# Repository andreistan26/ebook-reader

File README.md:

# OpenBook - Andrei Stan 331CC

## Descriere Functionalitate Hardware
- Tableta este controlata prin cele 3 butoane
- ESP-ul comunica cu memoria flash si SD card-ul
- Trimite date la display pentru afisarea continutului din flash/sd card
- De la USB se folosesc linia de date si cea de putere pentru alimentare
- Linia de alimentare incarca bateria tabletei
- Se folosesc protocoalele i2c si spi pentru comunicatie
- UART se poate folosi prin testpad-uri pentru debugging
## ESP32 Pini
|Pin|Semnal|Descriere|
|---|------|---------|
|EN|RESET|exact ce spune semanalul
|IO0|INT_RTC| conectat la modulul RTC care poate emite intreruperi la anumite alarme/timere
|IO1|32KHz| transmite un semanl de 32Khz care este folosit pentru ceasul tabletei
|IO2|MISO| pentru primirea datelor de la periferic (ex. SD card reader, Flash memorie)
|IO3|EPD_BUSY| pentru a trimite date numai atunci cand display-ul este gata de randat, epaper este incet, deci avem nevoie de acest semnal
|IO4|SS_SD| folosit pentru detectia sd cardului, daca este prezent
|IO5|EPD_DC| comunicatie seriala cu e-paper display-ul
|IO6|SCK| ceas pentru comunicatia SPI cu celelalte componente SPI
|IO7|MOSI| pentru transmisia informatiilor pentru card SD, memorie flash si display
|IO8|GPIO8| neutilizat
|IO9|IO/BOOT| a fost apasat butonul de pornire
|IO10|EPD_CS| Chip select pentru comunicatia seriala
|IO11|FLASH_CS| Chip select pentru memoria flash
|IO12|USB_D-| transfer de date USB diferential -
|IO13|USB_D+| transfer de date USB diferential +
|IO15|IO/Change| butonul de schimbat pagina este apasat
|TXD0| TX| Tx pe UART, este folosit numai la testpad-uri pentru debugging
|RXD0| RX| Rx pe UART, este folosit numai la testpad-uri  pentru debugging
|IO18| RTC_RST| resetare a ceasului de 32Khz
|IO19| I2C_PW| alimentare si chip-select pentru senzor
|IO20| EPD_3v3_c| controleaza transzistorul prin care este alimentat display-ul (nu putem alimenta direct din el sau cel putin e bad practice)
|IO21| SDA| linie de date pentru comunicarea i2c 
|IO22| SCL| semnalul de ceas pentru comunicatrea i2c
|IO23| EPD_RST| resetare a display-ului

## Design Log \ Decizii

* Mufa USB a fost modificata pentru a evita erorile DRC
* Traseele de putere au fost facute prima data, dupa care am folosit autorouter-ul pentru a completa
* Am mutat toate gaurile de pe carcasa si dimensiunile acesteia pentru a intra PCB ul

## BOM
|Qty|Device|Parts|DATASHEET|DESCRIPTION|MOUSER_PRICE-STOCK|
|---|------|-----|---------|-----------|------------------|
|1|ADAFRUIT_LEDCHIP-LED0603|CHG_LED|https://www.vishay.com/doc?82437||https://ro.mouser.com/ProductDetail/Vishay-Semiconductors/VLMY1301-GS08?qs=sGAEpiMZZMusoohG2hS%252B168PbK3WnfgfiGSE4pxVBaDPiKIho6Ieew%3D%3D|
|1|ESP32_WROVER_EAGLE-LTSPICE_RR0402|R15|https://www.vishay.com/doc?20035||https://ro.mouser.com/ProductDetail/Vishay-Dale/CRCW040240K2FKED?qs=rzhQWu8UUS3g49JmcwYN7w%3D%3D&utm_id=20109199409&utm_source=google&utm_medium=cpc&utm_marketing_tactic=emeacorp&gad_source=1&gclid=EAIaIQobChMI4vv9kZaojAMV7YKDBx2W9Ae5EAAYAiAAEgK9cfD_BwE|
|1|ESP32_WROVER_EAGLE-LTSPICE_RR0402|R21|https://www.vishay.com/doc?20035|||
|7|EAGLE-LTSPICE_CC0402|"C3, C4, C5, C9, C18, C19, C_DELAY"|https://ro.mouser.com/datasheet/2/447/KEM_C1006_X5R_SMD-3316465.pdf||https://ro.mouser.com/ProductDetail/KEMET/C0402C475K8PACTU?qs=sGAEpiMZZMsh%252B1woXyUXj%252BeMYF%2FJh1ZHWLnD7xub%252BoY%3D|
|2|ESP32_WROVER_EAGLE-LTSPICE_CC0402|"C24, C25"|https://ro.mouser.com/datasheet/2/447/KEM_C1006_X5R_SMD-3316465.pdf||https://ro.mouser.com/ProductDetail/KEMET/C0402C475K8PACTU?qs=sGAEpiMZZMsh%252B1woXyUXj%252BeMYF%2FJh1ZHWLnD7xub%252BoY%3D|
|1|RCL_CPOL-EUCT3528|C28|https://ro.mouser.com/datasheet/2/447/KEM_T2073_T59X-3316825.pdf||https://ro.mouser.com/ProductDetail/KEMET/T598B335M035ATE150?qs=sGAEpiMZZMsh%252B1woXyUXj9kQnrMN1UR3%252B%2FX%2FiUkAw%2Fg%3D|
|1|ESP32_WROVER_EAGLE-LTSPICE_RR0402|R14|https://www.vishay.com/doc?20035||https://ro.mouser.com/ProductDetail/Vishay-Dale/CRCW040240K2FKED?qs=rzhQWu8UUS3g49JmcwYN7w%3D%3D&utm_id=20109199409&utm_source=google&utm_medium=cpc&utm_marketing_tactic=emeacorp&gad_source=1&gclid=EAIaIQobChMI4vv9kZaojAMV7YKDBx2W9Ae5EAAYAiAAEgK9cfD_BwE|
|12|ESP32_WROVER_EAGLE-LTSPICE_RR0402|"R1, R1_PINH1, R2, R2_PINH1, R3, R5, R6, R7, R8, R10, R11, R17"|https://www.vishay.com/doc?20035|||
|3|ESP32_WROVER_EAGLE-LTSPICE_RR0402|"R_BOOT, R_CHANGE, R_RESET"|https://www.vishay.com/doc?20035|||
|1|ESP32_WROVER_EAGLE-LTSPICE_CC0402|C21|https://ro.mouser.com/datasheet/2/447/KEM_C1006_X5R_SMD-3316465.pdf||https://ro.mouser.com/ProductDetail/KEMET/C0402C475K8PACTU?qs=sGAEpiMZZMsh%252B1woXyUXj%252BeMYF%2FJh1ZHWLnD7xub%252BoY%3D|
|1|112A-TAAR-R03_ATTEND|J1|https://www.attend.com.tw/data/download/file/112A-TAAR-R03_Spec.pdf|"Micro SD Card Socket, Push-Push Type, Top Mount, SMT, H=1.83mm, 10u"|https://www.digikey.com/en/products/detail/attend-technology/112A-TAAR-R03/17633923|
|1|ESP32_WROVER_EAGLE-LTSPICE_RR0402|R_CAPACITOR|https://www.vishay.com/doc?20035|||
|1|EAGLE-LTSPICE_CC0402|C2|https://ro.mouser.com/datasheet/2/447/KEM_C1006_X5R_SMD-3316465.pdf||https://ro.mouser.com/ProductDetail/KEMET/C0402C475K8PACTU?qs=sGAEpiMZZMsh%252B1woXyUXj%252BeMYF%2FJh1ZHWLnD7xub%252BoY%3D|
|10|EAGLE-LTSPICE_CC0402|"C7, C8, C10, C11, C12, C13, C14, C15, C16, C17"|https://ro.mouser.com/datasheet/2/447/KEM_C1006_X5R_SMD-3316465.pdf||https://ro.mouser.com/ProductDetail/KEMET/C0402C475K8PACTU?qs=sGAEpiMZZMsh%252B1woXyUXj%252BeMYF%2FJh1ZHWLnD7xub%252BoY%3D|
|1|ESP32_WROVER_EAGLE-LTSPICE_RR0402|R12|https://www.vishay.com/doc?20035|||
|1|ESP32_WROVER_EAGLE-LTSPICE_RR0402|R1_BAT|https://www.vishay.com/doc?20035|||
|1|ESP32_WROVER_SPARKFUN-DISCRETESEMI_MOSFET_PCH-DMG2305UX-7|Q1|https://www.diodes.com/assets/Datasheets/DMG2305UX.pdf||https://www.digikey.ro/en/products/detail/diodes-incorporated/DMG2305UX-7/4340667|
|1|ESP32_WROVER_SPARKFUN-DISCRETESEMI_MOSFET_PCH-DMG2305UX-7|Q3|https://www.diodes.com/assets/Datasheets/DMG2305UX.pdf||https://www.digikey.ro/en/products/detail/diodes-incorporated/DMG2305UX-7/4340667|
|1|ESP32_WROVER_EAGLE-LTSPICE_RR0402|R16|https://www.vishay.com/doc?20035|||
|2|EAGLE-LTSPICE_CC0402|"C22, C23"|https://ro.mouser.com/datasheet/2/447/KEM_C1006_X5R_SMD-3316465.pdf||https://ro.mouser.com/ProductDetail/KEMET/C0402C475K8PACTU?qs=sGAEpiMZZMsh%252B1woXyUXj%252BeMYF%2FJh1ZHWLnD7xub%252BoY%3D|
|2|ESP32_WROVER_EAGLE-LTSPICE_CC0402|"C26, C27"|https://ro.mouser.com/datasheet/2/447/KEM_C1006_X5R_SMD-3316465.pdf||https://ro.mouser.com/ProductDetail/KEMET/C0402C475K8PACTU?qs=sGAEpiMZZMsh%252B1woXyUXj%252BeMYF%2FJh1ZHWLnD7xub%252BoY%3D|
|1|ESP32_WROVER_EAGLE-LTSPICE_CC0402|C20|https://ro.mouser.com/datasheet/2/447/KEM_C1006_X5R_SMD-3316465.pdf||https://ro.mouser.com/ProductDetail/KEMET/C0402C475K8PACTU?qs=sGAEpiMZZMsh%252B1woXyUXj%252BeMYF%2FJh1ZHWLnD7xub%252BoY%3D|
|2|ESP32_WROVER_EAGLE-LTSPICE_RR0402|"R19, R20"|https://www.vishay.com/doc?20035|||
|1|744043680IND_4828-WE-TPC_WRE|L3|https://www.we-online.com/components/products/datasheet/744043680.pdf||https://ro.mouser.com/ProductDetail/Wurth-Elektronik/744043680?qs=PGXP4M47uW6VkZq%252BkzjrHA%3D%3D&srsltid=AfmBOoq3PLABygfB0-85eEKpA9SffUYwty425nbkhbFJ01kDNoAxFF7J|
|1|BD5229G-TR|IC1|https://fscdn.rohm.com/en/products/databook/datasheet/ic/power/voltage_detector/bd52xxg-e.pdf|"Voltage Detector with Adjustable Delay Time: CMOS processes are utilized to develop high precision  low current consumption CMOS reset ICs that allow arbitrary setting of the delay time. The extensive lineup includes both Nch Open Drain and CMOS output types in a wide range of detection voltages (from 2.3V to 6.0V, in 0.1V steps) enabling selection of the ideal solution based on customer requirements. In addition the entire series is of course both lead-free and RoHS-compliant."|https://www.mouser.co.uk/ProductDetail/ROHM-Semiconductor/BD5229G-TR?qs=4kLU8WoGk0vvnhrrYwdszw%3D%3D|
|1|ESP32_WROVER_BME680_BME680|SENSOR2|https://ro.mouser.com/datasheet/2/783/BST_BME680_DS001-1509608.pdf| Integrated Environmental Unit |https://ro.mouser.com/ProductDetail/Bosch-Sensortec/BME680?qs=v271MhAjFHjo0yA%2FC4OnDQ%3D%3D|
|3|BUTTON_CUSYOMV1|"BOOT_BUTTON, CHANGE_BUTTON, RESET_BUTTON"|https://4donline.ihs.com/images/VipMasterIC/IC/PANA/PANAS45028/PANAS45028-1.pdf?hkey=CECEF36DEECDED6468708AAF2E19C0C6||https://ro.mouser.com/ProductDetail/Panasonic/EVQ-9P701P?qs=NPkb10g2yLBKCwpELvsGNg%3D%3D|
|1|CPH3225A|C6|https://mm.digikey.com/Volume0/opasdata/d220001/medias/docus/6537/rev05-CPHCPM.pdf| 11 mF (EDLC) Supercapacitor 3.3 V 1210 (3225 Metric) - - ||
|1|DS3231SN#|U4|https://ro.mouser.com/datasheet/2/609/DS3231-3421123.pdf| Extremely Accurate I C-Integrated RTC/TCXO/Crystal ||
|1|ESP32-C6-WROOM-1-N8|U1|https://www.espressif.com/sites/default/files/documentation/esp32-c6-wroom-1_wroom-1u_datasheet_en.pdf|" Multiprotocol Modules ESP32-C6 module, Wi-Fi 6 in 2.4 GHz band, Bluetooth 5, Zigbee 3.0 and Thread. ESP34-WROOM Compatible - ENGINEERING SAMPLE "||
|1|ESP32C6_VARISTORCN1812|R18|https://mm.digikey.com/Volume0/opasdata/d220001/medias/docus/2123/CTVS_Standard_Rev2015.pdf||https://www.digikey.be/en/products/detail/epcos-tdk-electronics/CN1812K11G/635074?srsltid=AfmBOora8jXqSIsuJ5wbLbjXOKEBe4X6EtjlDXrR_O7ItUtFQ009LUoi|
|2|ESP32_WROVER_AVX---SD0805S020S1R0_AVX_SD0805S020S1R0_0_0AVX_SD0805S020S1R0_0_0|"D1, D13"|http://datasheets.avx.com/schottky.pdf|||
|1|ESP32_WROVER_SPARKFUN-IC-POWER_MCP73831|MCP73831|https://ro.mouser.com/datasheet/2/268/MCP73831_Family_Data_Sheet_DS20001984H-3441711.pdf||https://www.mouser.dk/ProductDetail/Microchip-Technology/MCP73831T-3ACI-OT?qs=yUQqVecv4quInAWkk8YFWg%3D%3D|
|1|FH34SRJ-24S-0.5SH_99_|J3|https://ro.mouser.com/datasheet/2/185/FH34SRJ_24S_0_5SH_99__CL0580_1255_6_99_2DDrawing_0-1615044.pdf|"24 Position FFC, FPC Connector Contacts, Top and Bottom 0.020"" (0.50mm) Surface Mount, Right Angle"|https://www.mouser.co.uk/ProductDetail/Hirose-Connector/FH34SRJ-24S-0.5SH99?qs=vcbW%252B4%252BSTIpKBl5ap9J8Fw%3D%3D|
|1|MAX17048G+T10|U2|https://ro.mouser.com/datasheet/2/609/MAX17048_MAX17049-3469099.pdf| 3 A 1-Cell/2-Cell Fuel Gauge with ModelGauge ||
|3|MBR0530|"D3, D5, D7"|https://www.onsemi.cn/pdf/datasheet/mbr0530-d.pdf| Diode Schottky 30 V 500mA Surface Mount SOD-123 ||
|6|PGB1010603MR|"D2, D4, D6, D8, D10, D11"|https://www.littelfuse.com/assetdocs/pulseguard-esd-suppressors-pgb1-datasheet?assetguid=8a337998-d54d-466b-be4e-dc5bcd1f9321| 150V (Typ) Clamp - Ipp Tvs Diode Surface Mount 0603 (1608 Metric) ||
|1|QWIIC_CONNECTORJS-1MM|J2|https://ro.mouser.com/datasheet/2/813/Qwiic_Connector_Datasheet-1223982.pdf||https://ro.mouser.com/ProductDetail/SparkFun/PRT-14417?qs=wd5RIQLrsJhgdz%2FpmZ%2F3GQ%3D%3D&srsltid=AfmBOoqQ1oOwS9wen4cUg5-iBLh8Bm57R1iVLhkDmOc94Djde0aRxIcK|
|1|SAMACSYS_PARTS_USB4110-GF-A|J4|https://ro.mouser.com/datasheet/2/837/GCT_USB4110_Product_Drawing___20k_cycles-3455479.pdf|CONN USB 2.0 TYPE-C R/A SMT|https://www.mouser.co.uk/ProductDetail/GCT/USB4110-GF-A?qs=KUoIvG%2F9IlYiZvIXQjyJeA%3D%3D|
|1|SI1308EDL-T1-GE3|Q2|https://www.vishay.com/docs/63399/si1308edl.pdf|" Si1308EDL-T1-GE3 N-channel MOSFET Transistor, 1.5 A, 30 V, 3-Pin SC-70 Siliconix / Vishay SI1308EDL-T1-GE3 "||
|1|USBLC6-2SC6Y|D9|https://ro.mouser.com/datasheet/2/389/usblc6_2sc6y-1852505.pdf| 17V Clamp 5A (8/20 s) Ipp Tvs Diode Surface Mount SOT-23-6 |https://ro.mouser.com/ProductDetail/STMicroelectronics/USBLC6-2SC6Y?utm_campaign=mouser&qs=gNDSiZmRJS%2FOgDexvXkdow==&utm_medium=online&utm_source=snapedaonline&utm_content=model|
|1|W25Q512JVEIQ|U3|https://www.winbond.com/resource-files/W25Q512JV%20SPI%20RevB%2006252019%20KMS.pdf| FLASH - NOR Memory IC 512Mb (64M x 8) SPI - Quad I/O 133 MHz 8-WSON (8x6) ||
|1|XC6220A331MR-G|IC2|https://ro.mouser.com/datasheet/2/760/xc6220-3371556.pdf|LDO Voltage Regulators|https://www.mouser.co.uk/ProductDetail/Torex-Semiconductor/XC6220A331MR-G?qs=AsjdqWjXhJ8ZSWznL1J0gg%3D%3D|

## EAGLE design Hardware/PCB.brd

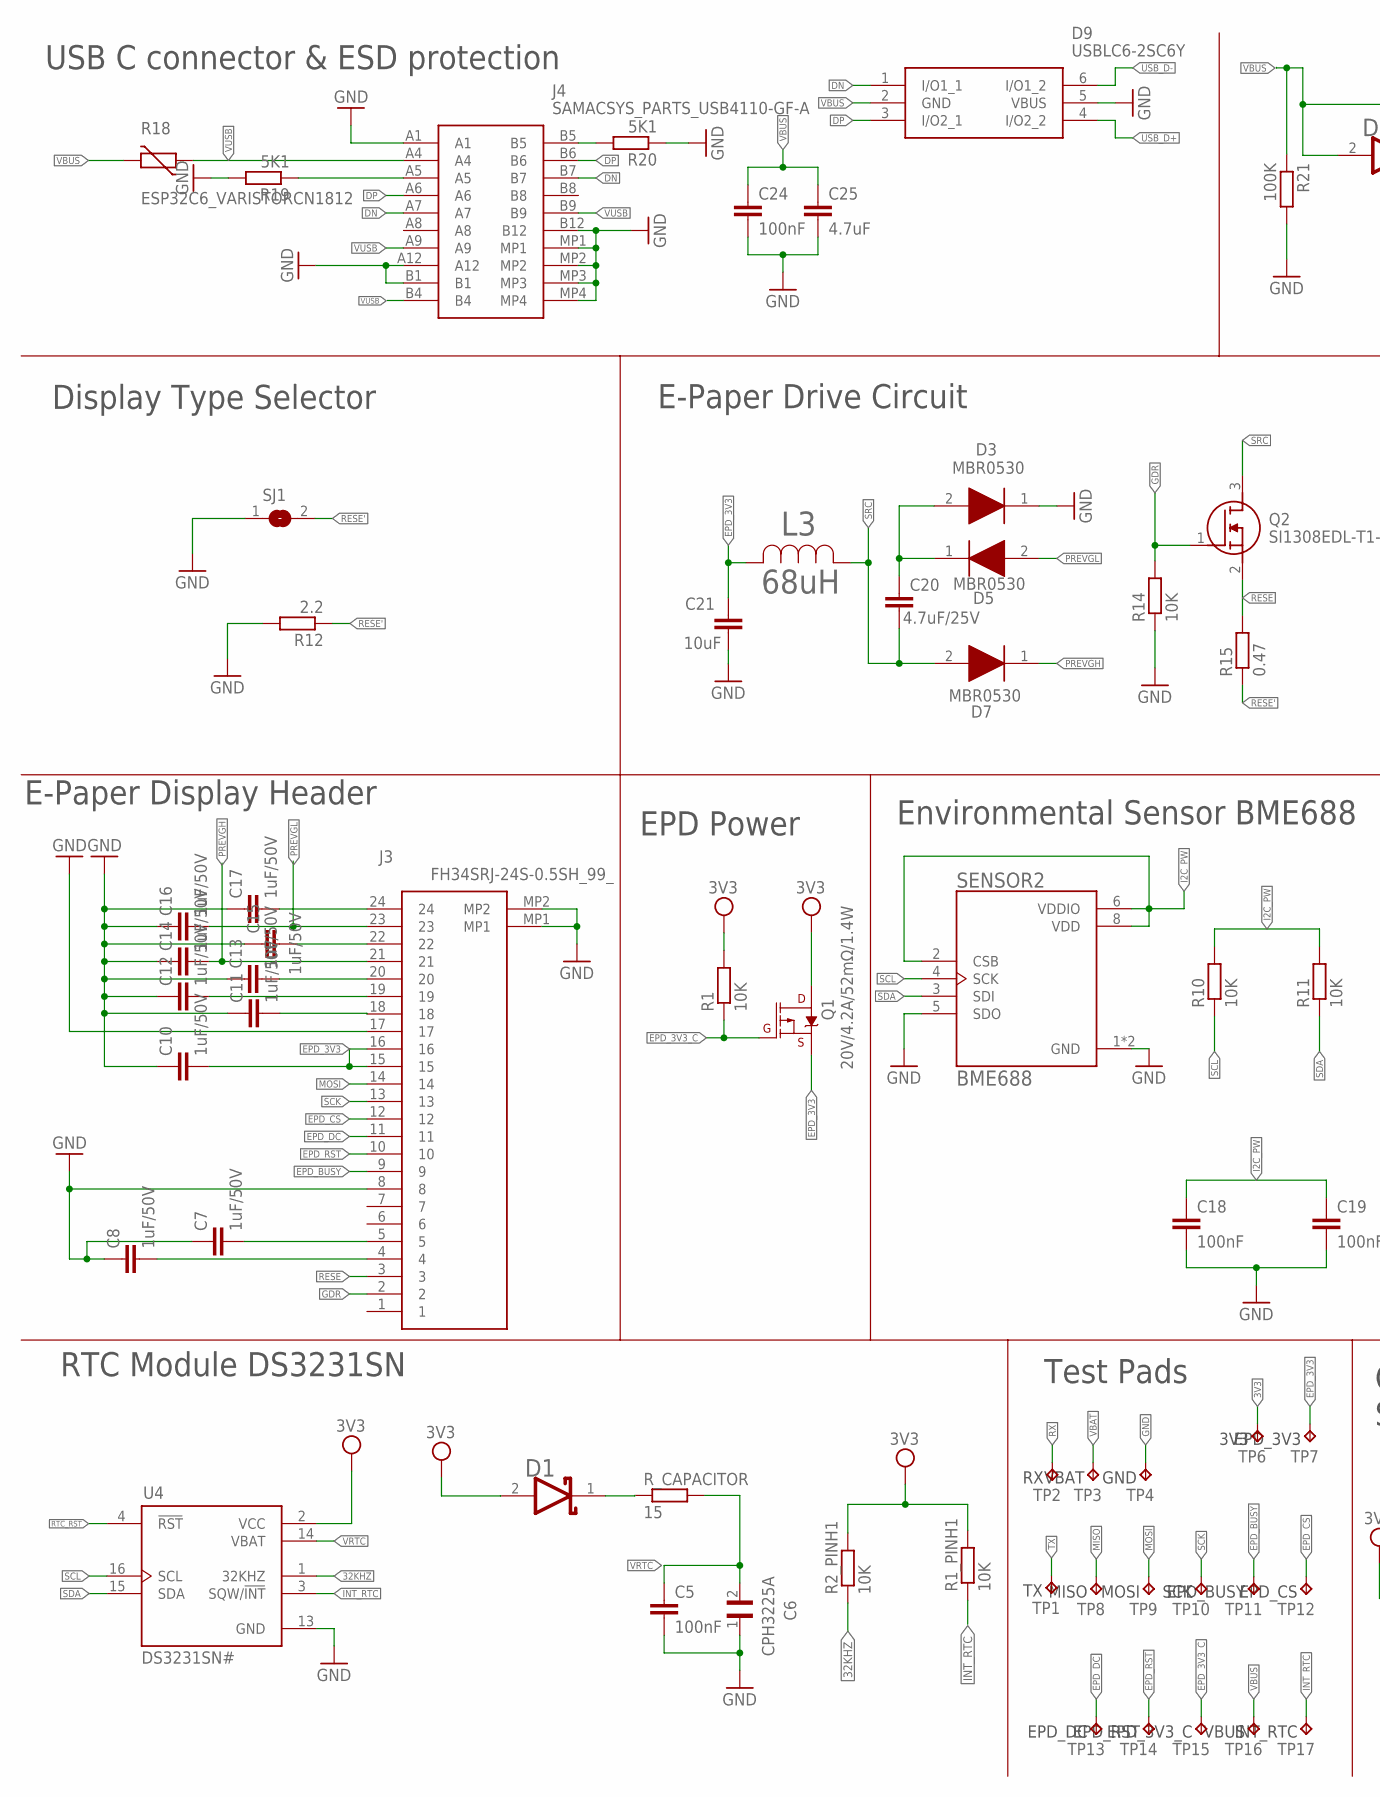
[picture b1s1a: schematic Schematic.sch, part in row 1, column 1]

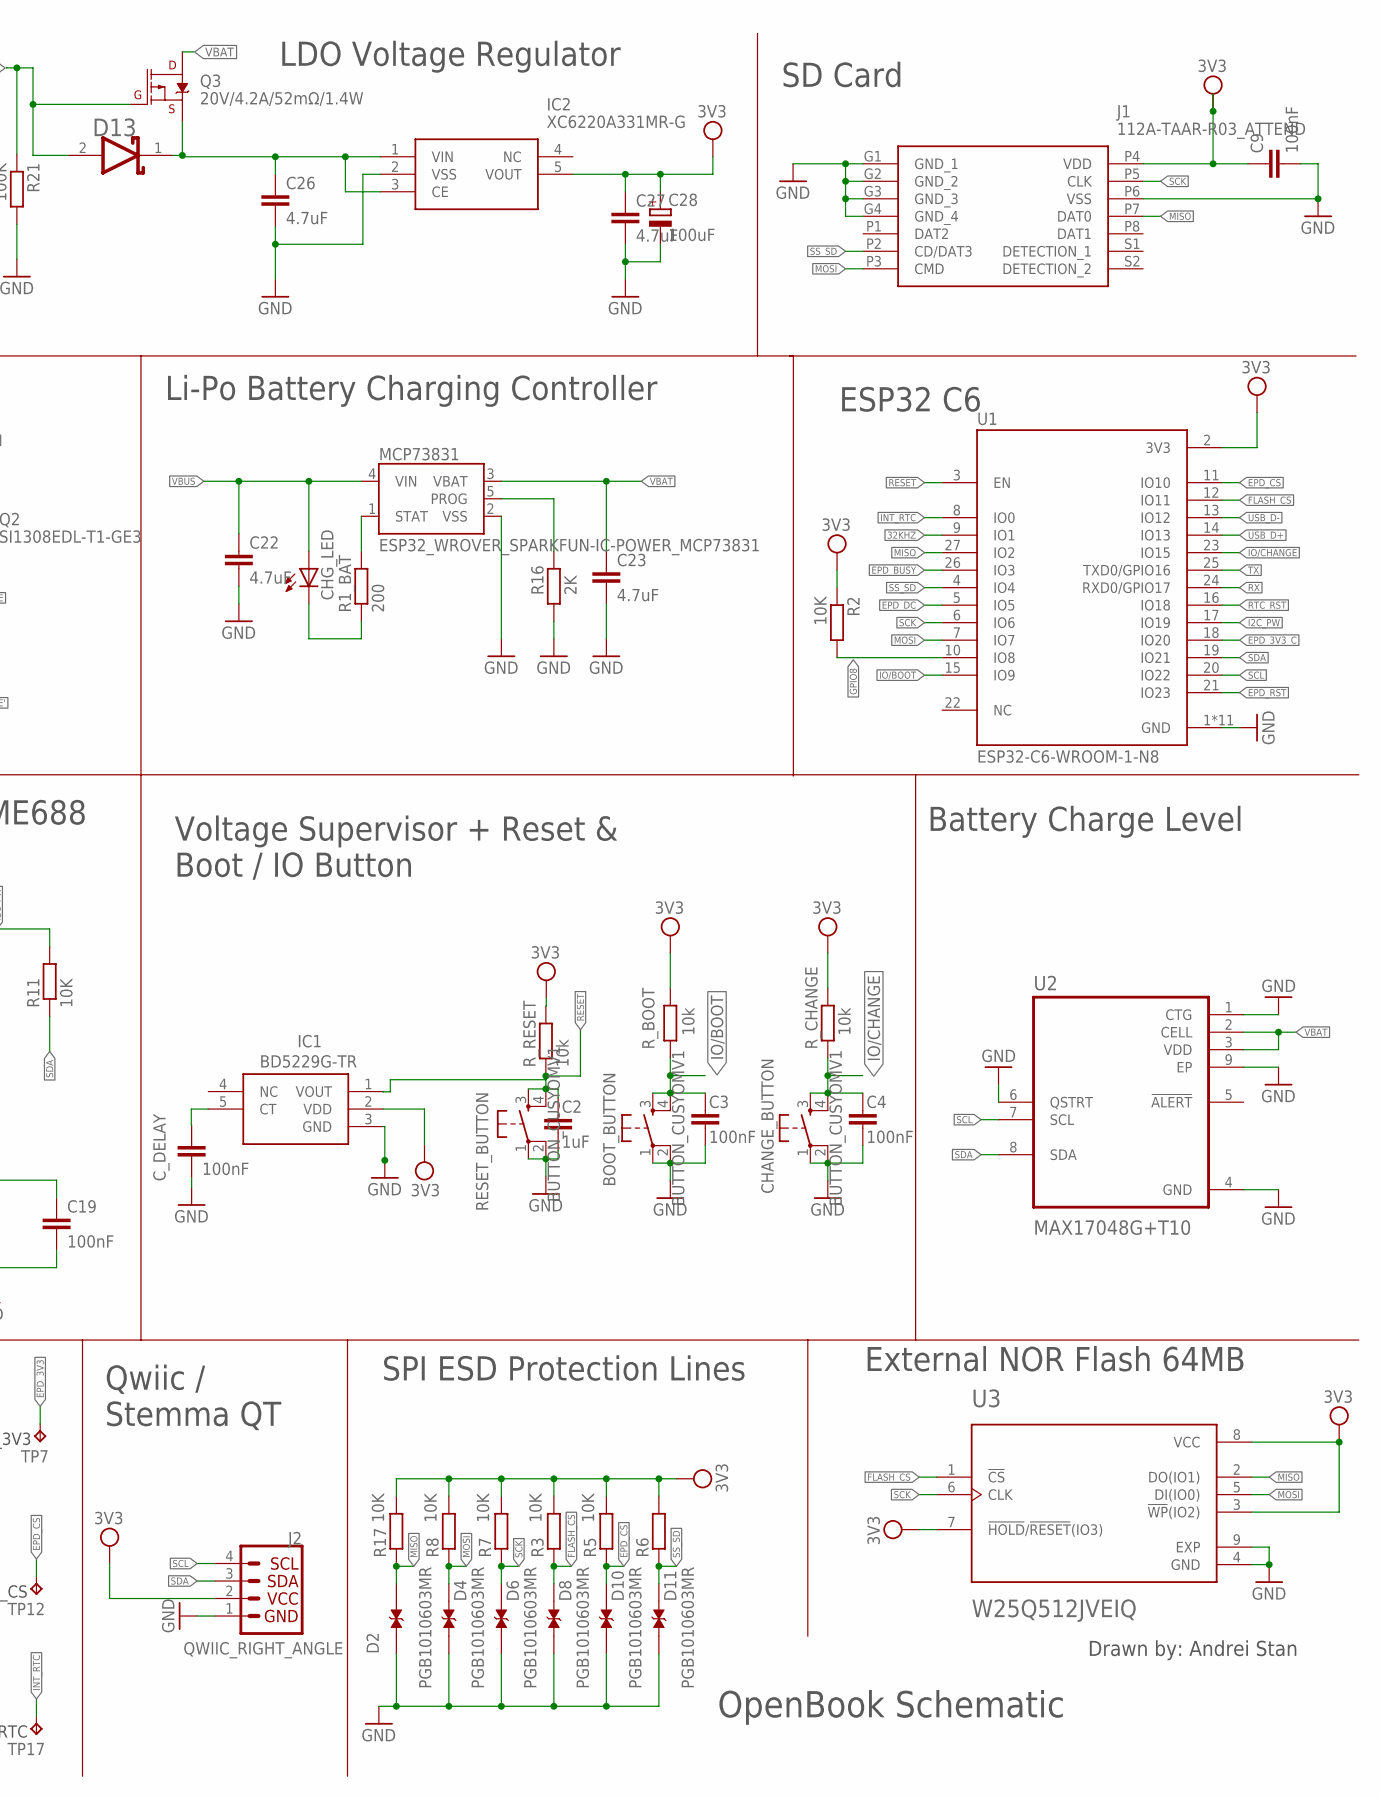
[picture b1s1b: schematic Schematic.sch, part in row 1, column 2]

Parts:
BOOT_BUTTON: BUTTON_CUSYOMV1; MYBUTTON
C2: 1uF; EAGLE-LTSPICE_C0402
C3, C4, C5, C9, C18, C19: 100nF; EAGLE-LTSPICE_C0402
C6: CPH3225A; CAPCP3225X100N
C7, C8, C10, C11, C12, C13, C14, C15, C16, C17: 1uF/50V; EAGLE-LTSPICE_C0402
C20: 4.7uF/25V; ESP32_WROVER_EAGLE-LTSPICE_C0402
C21: 10uF; ESP32_WROVER_EAGLE-LTSPICE_C0402
C22, C23: 4.7uF; EAGLE-LTSPICE_C0402
C24: 100nF; ESP32_WROVER_EAGLE-LTSPICE_C0402
C25, C26, C27: 4.7uF; ESP32_WROVER_EAGLE-LTSPICE_C0402
C28: 100uF; RCL_CT3528
CHANGE_BUTTON: BUTTON_CUSYOMV1; MYBUTTON
CHG_LED: ADAFRUIT_LEDCHIP-LED0603; ADAFRUIT_CHIP-LED0603
C_DELAY: 100nF; EAGLE-LTSPICE_C0402
D1, D13: ESP32_WROVER_AVX---SD0805S020S1R0_AVX_SD0805S020S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; ESP32_WROVER_AVX---SD0805S020S1R0_AVX_SD0805S020S1R0_0
D2, D4, D6, D8, D10, D11: PGB1010603MR; DIOC1608X36N
D3, D5, D7: MBR0530; SOD3716X135N
D9: USBLC6-2SC6Y; SOT95P280X145-6N
IC1: BD5229G-TR; SOT95P280X125-5N
IC2: XC6220A331MR-G; SOT95P280X120-5N
J1: 112A-TAAR-R03_ATTEND; 112ATAARR03ATTEND
J2: QWIIC_RIGHT_ANGLE; JST04_1MM_RA
J3: FH34SRJ-24S-0.5SH_99_; FH34SRJ24S05SH99
J4: SAMACSYS_PARTS_USB4110-GF-A; SAMACSYS_PARTS_USB4110GFA
L3: 68uH; IND_4828-WE-TPC_WRE
MCP73831: ESP32_WROVER_SPARKFUN-IC-POWER_MCP73831; ESP32_WROVER_SPARKFUN-IC-POWER_SOT23-5
Q1, Q3: 20V/4.2A/52mΩ/1.4W; ESP32_WROVER_SPARKFUN-DISCRETESEMI_SOT23-3
Q2: SI1308EDL-T1-GE3; SOT65P210X110-3N
R1, R1_PINH1, R2, R2_PINH1, R3, R5, R6, R7, R8, R10, R11, R14, R17: 10K; ESP32_WROVER_EAGLE-LTSPICE_R0402
R1_BAT: 200; ESP32_WROVER_EAGLE-LTSPICE_R0402
R12: 2.2; ESP32_WROVER_EAGLE-LTSPICE_R0402
R15: 0.47; ESP32_WROVER_EAGLE-LTSPICE_R0402
R16: 2K; ESP32_WROVER_EAGLE-LTSPICE_R0402
R18: ESP32C6_VARISTORCN1812; ESP32C6_VARISTOR_CT/CN1812
R19, R20: 5K1; ESP32_WROVER_EAGLE-LTSPICE_R0402
R21: 100K; ESP32_WROVER_EAGLE-LTSPICE_R0402
RESET_BUTTON: BUTTON_CUSYOMV1; MYBUTTON
R_BOOT: 10k; ESP32_WROVER_EAGLE-LTSPICE_R0402
R_CAPACITOR: 15; ESP32_WROVER_EAGLE-LTSPICE_R0402
R_CHANGE: 10k; ESP32_WROVER_EAGLE-LTSPICE_R0402
R_RESET: 10k; ESP32_WROVER_EAGLE-LTSPICE_R0402
SENSOR2: BME688; ESP32_WROVER_BME680_PSON80P300X300X100-8N
SJ1: SJ
TP1, TP2, TP3, TP4, TP6, TP7, TP8, TP9, TP10, TP11, TP12, TP13, TP14, TP15, TP16, TP17: TPTP20R; TP20R
U1: ESP32-C6-WROOM-1-N8; XCVR_ESP32-C6-WROOM-1-N8
U2: MAX17048G+T10; SON50P200X200X80-9N
U3: W25Q512JVEIQ; SON127P600X800X80-9N
U4: DS3231SN#; SOIC127P1032X265-16N

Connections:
3V3: C9.1, C27.1, C28.+, D1.2 (ANODE), IC1.2 (VDD), IC2.5 (VOUT), J1.P4 (VDD), J2.2, Q1.3 (D), R1.2, R1_PINH1.2, R2.1, R2_PINH1.2, R3.2, R5.2, R6.2, R7.2, R8.2, R17.2, R_BOOT.2, R_CHANGE.2, R_RESET.2, TP6.TP, U1.2 (3V3), U3.3 (!WP!(IO2)), U3.7 (!HOLD!/!RESET!(IO3)), U3.8 (VCC), U4.2 (VCC)
32KHZ: R2_PINH1.1, U1.9 (IO1), U4.1 (32KHZ)
DN: D9.1 (I/O1_1), J4.A7, J4.B7
DP: D9.3 (I/O2_1), J4.A6, J4.B6
EPD_3V3: C10.2, C21.1, J3.15, J3.16, L3.2, Q1.2 (S), TP7.TP
EPD_3V3_C: Q1.1 (G), R1.1, TP15.TP, U1.18 (IO20)
EPD_BUSY: J3.9, TP11.TP, U1.26 (IO3)
EPD_CS: D10.2, J3.12, R5.1, TP12.TP, U1.11 (IO10)
EPD_DC: J3.11, TP13.TP, U1.5 (IO5)
EPD_RST: J3.10, TP14.TP, U1.21 (IO23)
FLASH_CS: D8.2, R3.1, U1.12 (IO11), U3.1 (!CS)
GDR: J3.2, Q2.1 (G), R14.2
GND: BOOT_BUTTON.1, BOOT_BUTTON.2, C2.2, C3.2, C4.2, C5.2, C6.1, C7.1, C8.1, C9.2, C10.1, C11.1, C12.1, C13.1, C14.1, C15.1, C16.1, C17.1, C18.2, C19.2, C21.2, C22.2, C23.2, C24.2, C25.2, C26.2, C27.2, C28.-, CHANGE_BUTTON.1, CHANGE_BUTTON.2, C_DELAY.2, D2.1, D3.1 (K), D4.1, D6.1, D8.1, D9.5 (VBUS), D10.1, D11.1, IC1.3 (GND), IC2.2 (VSS), J1.G1 (GND_1), J1.G2 (GND_2), J1.G3 (GND_3), J1.G4 (GND_4), J1.P6 (VSS), J2.1, J3.8, J3.17, J3.MP1, J3.MP2, J4.A1, J4.A12, J4.B1, J4.B12, J4.MP1, J4.MP2, J4.MP3, J4.MP4, MCP73831.2 (VSS), R12.2, R14.1, R16.1, R19.2, R20.1, R21.2, RESET_BUTTON.1, RESET_BUTTON.2, SENSOR2.1 (GND), SENSOR2.5 (SDO), SENSOR2.7 (GND), SJ1.1, TP4.TP, U1.1 (GND), U1.28 (GND), U1.29_1 (GND), U1.29_2 (GND), U1.29_3 (GND), U1.29_4 (GND), U1.29_5 (GND), U1.29_6 (GND), U1.29_7 (GND), U1.29_8 (GND), U1.29_9 (GND), U2.1 (CTG), U2.4 (GND), U2.6 (QSTRT), U2.9 (EP), U3.4 (GND), U3.9 (EXP), U4.13 (GND)
GPIO8: R2.2, U1.10 (IO8)
I2C_PW: C18.1, C19.1, R10.2, R11.2, SENSOR2.2 (CSB), SENSOR2.6 (VDDIO), SENSOR2.8 (VDD), U1.17 (IO19)
INT_RTC: R1_PINH1.1, TP17.TP, U1.8 (IO0), U4.3 (SQW/!INT)
IO/BOOT: BOOT_BUTTON.3, BOOT_BUTTON.4, C3.1, R_BOOT.1, U1.15 (IO9)
IO/CHANGE: C4.1, CHANGE_BUTTON.3, CHANGE_BUTTON.4, R_CHANGE.1, U1.23 (IO15)
MISO: D2.2, J1.P7 (DAT0), R17.1, TP8.TP, U1.27 (IO2), U3.2 (DO(IO1))
MOSI: D4.2, J1.P3 (CMD), J3.14, R8.1, TP9.TP, U1.7 (IO7), U3.5 (DI(IO0))
unnamed: C_DELAY.1, IC1.5 (CT)
unnamed: D1.1 (CATHODE), R_CAPACITOR.1
unnamed: C8.2, J3.4
unnamed: C7.2, J3.5
unnamed: C20.1, D3.2 (A), D5.1 (K)
unnamed: MCP73831.1 (STAT), R1_BAT.2
unnamed: J4.A5, R19.1
unnamed: CHG_LED.C, R1_BAT.1
unnamed: MCP73831.5 (PROG), R16.2
unnamed: J4.B5, R20.2
unnamed: C26.1, D13.1 (CATHODE), IC2.1 (VIN), IC2.3 (CE), Q3.2 (S)
unnamed: C11.2, J3.18
unnamed: C12.2, J3.19
unnamed: C13.2, J3.20
unnamed: C15.2, J3.22
unnamed: C17.2, J3.24
PREVGH: C14.2, D7.1 (K), J3.21
PREVGL: C16.2, D5.2 (A), J3.23
RESE: J3.3, Q2.2 (S), R15.2
RESE': R12.1, R15.1, SJ1.2
RESET: C2.1, IC1.1 (VOUT), RESET_BUTTON.3, RESET_BUTTON.4, R_RESET.1, U1.3 (EN)
RTC_RST: U1.16 (IO18), U4.4 (!RST)
RX: TP2.TP, U1.24 (RXD0/GPIO17)
SCK: D6.2, J1.P5 (CLK), J3.13, R7.1, TP10.TP, U1.6 (IO6), U3.6 (CLK)
SCL: J2.4, R10.1, SENSOR2.4 (SCK), U1.20 (IO22), U2.7 (SCL), U4.16 (SCL)
SDA: J2.3, R11.1, SENSOR2.3 (SDI), U1.19 (IO21), U2.8 (SDA), U4.15 (SDA)
SRC: C20.2, D7.2 (A), L3.1, Q2.3 (D)
SS_SD: D11.2, J1.P2 (CD/DAT3), R6.1, U1.4 (IO4)
TX: TP1.TP, U1.25 (TXD0/GPIO16)
USB_D+: D9.4 (I/O2_2), U1.14 (IO13)
USB_D-: D9.6 (I/O1_2), U1.13 (IO12)
VBAT: C23.1, MCP73831.3 (VBAT), Q3.3 (D), TP3.TP, U2.2 (CELL), U2.3 (VDD)
VBUS: C22.1, C24.1, C25.1, CHG_LED.A, D9.2 (GND), D13.2 (ANODE), MCP73831.4 (VIN), Q3.1 (G), R18.2, R21.1, TP16.TP
VRTC: C5.1, C6.2, R_CAPACITOR.2, U4.14 (VBAT)
VUSB: J4.A4, J4.A9, J4.B4, J4.B9, R18.1

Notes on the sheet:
OpenBook Schematic
Drawn by: Andrei Stan
External NOR Flash 64MB
Battery Charge Level
ESP32 C6
SD Card
Qwiic / Stemma QT
SPI ESD Protection Lines
Test Pads
RTC Module DS3231SN
E-Paper Display Header
EPD Power
Voltage Supervisor + Reset & Boot / IO Button
Environmental Sensor BME688
Li-Po Battery Charging Controller
E-Paper Drive Circuit
LDO Voltage Regulator
Display Type Selector
USB C connector & ESD protection

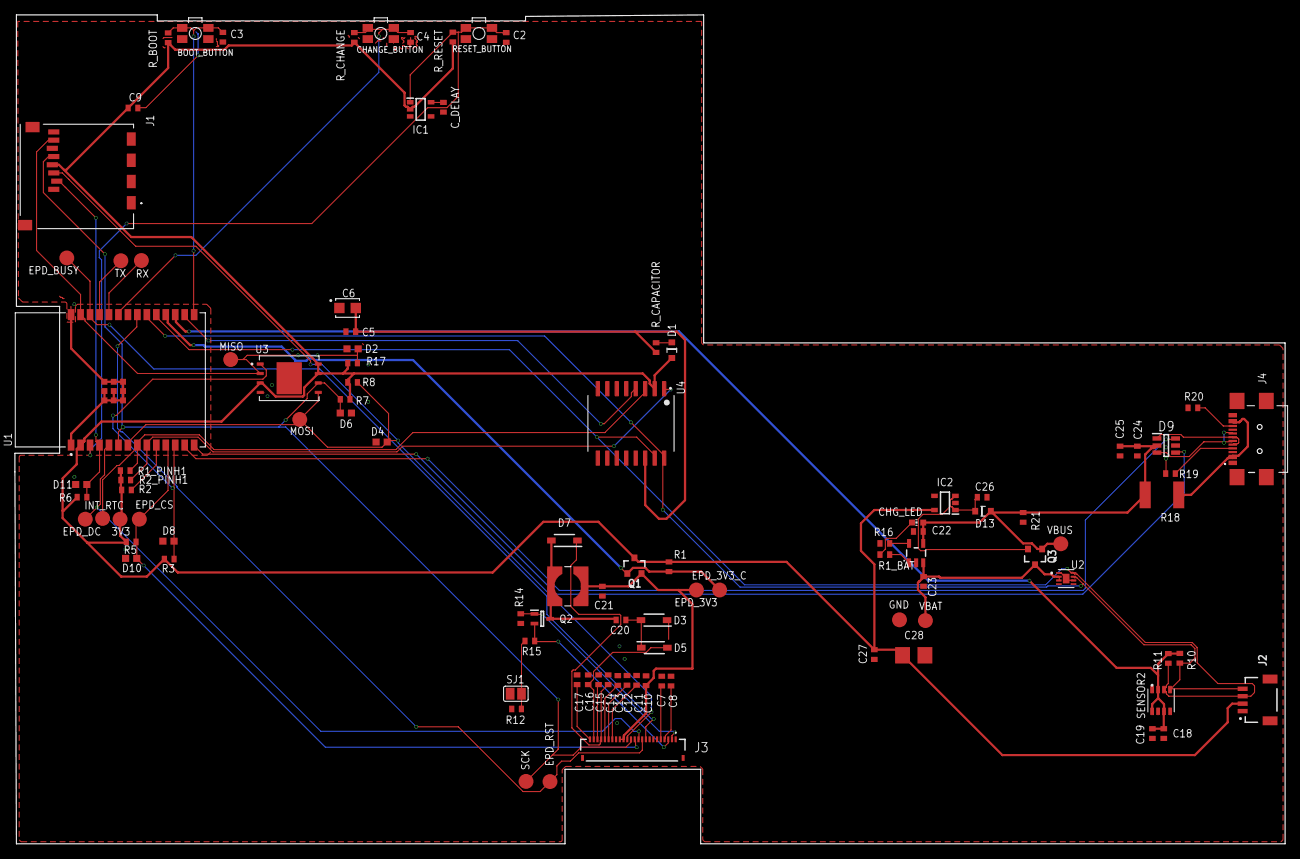
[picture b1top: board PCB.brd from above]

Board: 2 copper layers, 170.4 x 111.2 mm, 102 parts (0 on the bottom side), 55 nets.

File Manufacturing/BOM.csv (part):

Qty,Value,Device,Package,Parts,Description,ARROW_PART_NUMBER,ARROW_PRICE-STOCK,AVAILABILITY,CENTROID_NOT_SPECIFIED,CHECK_PRICES,COPYRIGHT,DATASHEET,DESCRIPTION,DIGIKEY_DESCRIPTION,DIGIKEY_PART_NUMBER,HEIGHT,LEAD_FREE,MANUFACTURER_NAME,MANUFACTURER_PART_NUMBER,MF,MFR_NAME,MOUSER_PART_NUMBER,MOUSER_PRICE-STOCK,MOUSER_TESTING_PART_NUMBER,MOUSER_TESTING_PRICE-STOCK,MP,MPN,PACKAGE,POPULARITY,PREFIX,PRICE,PROD_ID,PURCHASE-URL,ROHS,SNAPEDA_LINK,SPICEMODEL,SPICEPREFIX,TEMPERATURE_RANGE_HIGH,TEMPERATURE_RANGE_LOW,TP_SIGNAL_NAME,VALUE
1,,ADAFRUIT_LEDCHIP-LED0603,ADAFRUIT_CHIP-LED0603,CHG_LED,LED,,,,,,,https://www.vishay.com/doc?82437,,,,,,,,,,,https://ro.mouser.com/ProductDetail/Vishay-Semiconductors/VL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,,,,,,,,,,,,,,,,,,
1,,SJ,SJ,SJ1,"SMD solder JUMPER",,,,,,,,,,,,,,,,,,,,,,,,3,,,,,,,,,,,,
1,0.47,ESP32_WROVER_EAGLE-LTSPICE_RR0402,ESP32_WROVER_EAGLE-LTSPICE_R0402,R15,"RESISTOR, European symbol",,,,,,,https://www.vishay.com/doc?20035,,,,,,,,,,,https://ro.mouser.com/ProductDetail/Vishay-Dale/CRCW040240K2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,,,,,,,,,,,,,NONE,R,,,,
1,100K,ESP32_WROVER_EAGLE-LTSPICE_RR0402,ESP32_WROVER_EAGLE-LTSPICE_R0402,R21,"RESISTOR, European symbol",,,,,,,https://www.vishay.com/doc?20035,,,,,,,,,,https://eu.mouser.com/ProductDetail/Vishay-Dale/CRCW040240K2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,,,,,,,,,,,,,,NONE,R,,,,
7,100nF,EAGLE-LTSPICE_CC0402,EAGLE-LTSPICE_C0402,"C3, C4, C5, C9, C18, C19, C_DELAY","CAPACITOR, European symbol",,,,,,,https://ro.mouser.com/datasheet/2/447/KEM_C1006_X5R_SMD-3316465.pdf,,,,,,,,,,,https://ro.mouser.com/ProductDetail/KEMET/C0402C475K8PACTU?q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,,,,,,,,,,,,,NONE,C,,,,
2,100nF,ESP32_WROVER_EAGLE-LTSPICE_CC0402,ESP32_WROVER_EAGLE-LTSPICE_C0402,"C24, C25","CAPACITOR, European symbol",,,,,,,https://ro.mouser.com/datasheet/2/447/KEM_C1006_X5R_SMD-3316465.pdf,,,,,,,,,,,https://ro.mouser.com/ProductDetail/KEMET/C0402C475K8PACTU?q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,,,,,,,,,,,,,NONE,C,,,,
1,100uF,RCL_CPOL-EUCT3528,RCL_CT3528,C28,"POLARIZED CAPACITOR, European symbol",,,,,,,https://ro.mouser.com/datasheet/2/447/KEM_T2073_T59X-3316825.pdf,,,,,,,,,,,https://ro.mouser.com/ProductDetail/KEMET/T598B335M035ATE150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,,,,,,0,,,,,,,,C,,,,
1,10K,ESP32_WROVER_EAGLE-LTSPICE_RR0402,ESP32_WROVER_EAGLE-LTSPICE_R0402,R14,"RESISTOR, European symbol",,,,,,,https://www.vishay.com/doc?20035,,,,,,,,,,,https://ro.mouser.com/ProductDetail/Vishay-Dale/CRCW040240K2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,,,,,,,,,,,,,NONE,R,,,,
12,10K,ESP32_WROVER_EAGLE-LTSPICE_RR0402,ESP32_WROVER_EAGLE-LTSPICE_R0402,"R1, R1_PINH1, R2, R2_PINH1, R3, R5, R6, R7, R8, R10, R11, R17","RESISTOR, European symbol",,,,,,,https://www.vishay.com/doc?20035,,,,,,,,,,https://eu.mouser.com/ProductDetail/Vishay-Dale/CRCW040240K2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,,,,,,,,,,,,,,NONE,R,,,,
3,10k,ESP32_WROVER_EAGLE-LTSPICE_RR0402,ESP32_WROVER_EAGLE-LTSPICE_R0402,"R_BOOT, R_CHANGE, R_RESET","RESISTOR, European symbol",,,,,,,https://www.vishay.com/doc?20035,,,,,,,,,,https://eu.mouser.com/ProductDetail/Vishay-Dale/CRCW040240K2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,,,,,,,,,,,,,,NONE,R,,,,
1,10uF,ESP32_WROVER_EAGLE-LTSPICE_CC0402,ESP32_WROVER_EAGLE-LTSPICE_C0402,C21,"CAPACITOR, European symbol",,,,,,,https://ro.mouser.com/datasheet/2/447/KEM_C1006_X5R_SMD-3316465.pdf,,,,,,,,,,,https://ro.mouser.com/ProductDetail/KEMET/C0402C475K8PACTU?q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,,,,,,,,,,,,,NONE,C,,,,
1,112A-TAAR-R03_ATTEND,112A-TAAR-R03_ATTEND,112ATAARR03ATTEND,J1,"Micro SD Card Socket, Push-Push Type, Top Mount, SMT, H=1.83mm, 10u",,,,,,,https://www.attend.com.tw/data/download/file/112A-TAAR-R03_Spec.pdf,"Micro SD Card Socket"," Push-Push Type"," Top Mount"," SMT"," H=1.83mm"," 10u",,,1.9mm,,ATTEND,"112A-TAAR-R03 ATTEND",,,,https://www.digikey.com/en/products/detail/attend-technology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,,,,,,,,,,,,,
1,15,ESP32_WROVER_EAGLE-LTSPICE_RR0402,ESP32_WROVER_EAGLE-LTSPICE_R0402,R_CAPACITOR,"RESISTOR, European symbol",,,,,,,https://www.vishay.com/doc?20035,,,,,,,,,,https://eu.mouser.com/ProductDetail/Vishay-Dale/CRCW040240K2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,,,,,,,,,,,,,,NONE,R,,,,
1,1uF,EAGLE-LTSPICE_CC0402,EAGLE-LTSPICE_C0402,C2,"CAPACITOR, European symbol",,,,,,,https://ro.mouser.com/datasheet/2/447/KEM_C1006_X5R_SMD-3316465.pdf,,,,,,,,,,,https://ro.mouser.com/ProductDetail/KEMET/C0402C475K8PACTU?q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,,,,,,,,,,,,,NONE,C,,,,
10,1uF/50V,EAGLE-LTSPICE_CC0402,EAGLE-LTSPICE_C0402,"C7, C8, C10, C11, C12, C13, C14, C15, C16, C17","CAPACITOR, European symbol",,,,,,,https://ro.mouser.com/datasheet/2/447/KEM_C1006_X5R_SMD-3316465.pdf,,,,,,,,,,,https://ro.mouser.com/ProductDetail/KEMET/C0402C475K8PACTU?q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,,,,,,,,,,,,,NONE,C,,,,
1,2.2,ESP32_WROVER_EAGLE-LTSPICE_RR0402,ESP32_WROVER_EAGLE-LTSPICE_R0402,R12,"RESISTOR, European symbol",,,,,,,https://www.vishay.com/doc?20035,,,,,,,,,,https://eu.mouser.com/ProductDetail/Vishay-Dale/CRCW040240K2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,,,,,,,,,,,,,,NONE,R,,,,
1,200,ESP32_WROVER_EAGLE-LTSPICE_RR0402,ESP32_WROVER_EAGLE-LTSPICE_R0402,R1_BAT,"RESISTOR, European symbol",,,,,,,https://www.vishay.com/doc?20035,,,,,,,,,,https://eu.mouser.com/ProductDetail/Vishay-Dale/CRCW040240K2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,,,,,,,,,,,,,,NONE,R,,,,
2,20V/4.2A/52mO/1.4W,ESP32_WROVER_SPARKFUN-DISCRETESEMI_MOSFET_PCH-DMG2305UX-7,ESP32_WROVER_SPARKFUN-DISCRETESEMI_SOT23-3,"Q1, Q3","P-channel MOSFETs",,,,,,,https://www.diodes.com/assets/Datasheets/DMG2305UX.pdf,,,,,,,,,,,https://www.digikey.ro/en/products/detail/diodes-incorporate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,,,,,,,,,TRAN-14388,,,,,,,,,20V/4.2A/52mO/1.4W
1,2K,ESP32_WROVER_EAGLE-LTSPICE_RR0402,ESP32_WROVER_EAGLE-LTSPICE_R0402,R16,"RESISTOR, European symbol",,,,,,,https://www.vishay.com/doc?20035,,,,,,,,,,https://eu.mouser.com/ProductDetail/Vishay-Dale/CRCW040240K2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,,,,,,,,,,,,,,NONE,R,,,,
2,4.7uF,EAGLE-LTSPICE_CC0402,EAGLE-LTSPICE_C0402,"C22, C23","CAPACITOR, European symbol",,,,,,,https://ro.mouser.com/datasheet/2/447/KEM_C1006_X5R_SMD-3316465.pdf,,,,,,,,,,,https://ro.mouser.com/ProductDetail/KEMET/C0402C475K8PACTU?q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,,,,,,,,,,,,,NONE,C,,,,
2,4.7uF,ESP32_WROVER_EAGLE-LTSPICE_CC0402,ESP32_WROVER_EAGLE-LTSPICE_C0402,"C26, C27","CAPACITOR, European symbol",,,,,,,https://ro.mouser.com/datasheet/2/447/KEM_C1006_X5R_SMD-3316465.pdf,,,,,,,,,,,https://ro.mouser.com/ProductDetail/KEMET/C0402C475K8PACTU?q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,,,,,,,,,,,,,NONE,C,,,,
1,4.7uF/25V,ESP32_WROVER_EAGLE-LTSPICE_CC0402,ESP32_WROVER_EAGLE-LTSPICE_C0402,C20,"CAPACITOR, European symbol",,,,,,,https://ro.mouser.com/datasheet/2/447/KEM_C1006_X5R_SMD-3316465.pdf,,,,,,,,,,,https://ro.mouser.com/ProductDetail/KEMET/C0402C475K8PACTU?q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,,,,,,,,,,,,,NONE,C,,,,
2,5K1,ESP32_WROVER_EAGLE-LTSPICE_RR0402,ESP32_WROVER_EAGLE-LTSPICE_R0402,"R19, R20","RESISTOR, European symbol",,,,,,,https://www.vishay.com/doc?20035,,,,,,,,,,https://eu.mouser.com/ProductDetail/Vishay-Dale/CRCW040240K2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,,,,,,,,,,,,,,NONE,R,,,,
1,68uH,744043680IND_4828-WE-TPC_WRE,IND_4828-WE-TPC_WRE,L3,,,,,,,"Copyright (C) 2024 Ultra Librarian. All rights reserved.",https://www.we-online.com/components/products/datasheet/7440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,,,,,,,744043680,,"Wurth Electronics",,https://ro.mouser.com/ProductDetail/Wurth-Elektronik/7440436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,,,,,,,,,,,,,,,,,,
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
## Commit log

2025-04-05 Add license
2025-04-05 Add gerber.zip
2025-04-14 fix issues

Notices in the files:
parts and their libraries:
COPYRIGHT: Copyright (C) 2024 Ultra Librarian. All rights reserved.
